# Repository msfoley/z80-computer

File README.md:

# z80-computer
Single board computer based on the Zilog Z80 processor

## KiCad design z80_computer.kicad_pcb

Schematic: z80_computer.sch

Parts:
C1, C3: 22p; CP_Radial_D5.0mm_P2.50mm; Part Number K220J15C0GF5TL2
C2: 100n; CP_Radial_D8.0mm_P5.00mm
C4: 10u; CP_Radial_D8.0mm_P5.00mm
C5: 10u; CP_Radial_D8.0mm_P5.00mm; Part Numer C322C106K3R5TA
J1: Screw_Terminal_01x02; TerminalBlock_RND_205-00001_1x02_P5.00mm_Horizontal
J2: Bus_ISA_8bit; PinHeader_2x31_P2.54mm_Vertical
R1: 1M; R_Axial_DIN0207_L6.3mm_D2.5mm_P5.08mm_Vertical; Part Number CF14JT1M00
R2: 1k; R_Axial_DIN0207_L6.3mm_D2.5mm_P5.08mm_Vertical; Part Number CF14JT1K00
R3: 720; R_Axial_DIN0207_L6.3mm_D2.5mm_P5.08mm_Vertical
R4: 240; R_Axial_DIN0207_L6.3mm_D2.5mm_P5.08mm_Vertical
R5, R6, R7, R8: 10k; R_Axial_DIN0207_L6.3mm_D2.5mm_P5.08mm_Vertical; Part Number CF14JT10K0
R9: 10K; R_Axial_DIN0207_L6.3mm_D2.5mm_P5.08mm_Vertical
U1: 74LS14; DIP-14_W7.62mm
U2: MCP130; TO-92
U3: LM117_TO3; TO-3
U5: Z80CPU; DIP-40_W15.24mm
U8: 74138; DIP-16_W7.62mm
Y1: Crystal; Crystal_HC49-U_Vertical; Part Number GB1000015

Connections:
+5V: C4.1, C5.2, J2.3, J2.29, R4.1, R5.1, R6.1, R7.1, R8.1, U1.14 (VCC), U2.2, U3.3 (VO), U5.11, U8.16; also elsewhere on the board
/A0: J2.62, U5.30
/A1: J2.61, U5.31
/A2: J2.60, U5.32
/A3: J2.59, U5.33
/A4: J2.58, U5.34
/A5: J2.57, U5.35, U8.1
/A6: J2.56, U5.36, U8.2
/A7: J2.55, U5.37, U8.3
/A8: J2.54, U5.38
/A9: J2.53, U5.39
/A10: J2.52, U5.40
/A11: J2.51, U5.1
/A12: J2.50, U5.2
/A13: J2.49, U5.3
/A14: J2.48, U5.4
/A15: J2.47, U5.5
/D0: J2.40, U5.14
/D1: J2.39, U5.15
/D2: J2.38, U5.12
/D3: J2.37, U5.8
/D4: J2.36, U5.7
/D5: J2.35, U5.9
/D6: J2.34, U5.10
/D7: J2.33, U5.13
/DS0: U8.15
/DS1: U8.14
/DS2: U8.13
/DS3: U8.12
/DS4: U8.11
/DS5: U8.10
/DS6: U8.9
/DS7: U8.7
/~BUSACK: U5.23
/~BUSRQ: R8.2, U5.25
/~CLK: J2.20, U1.4, U5.6
/~HALT: U5.18
/~INT: R7.2, U5.16
/~IORD: J2.14; also elsewhere on the board
/~IORQ: U5.20, U8.4, U8.5; also elsewhere on the board
/~IOWR: J2.13; also elsewhere on the board
/~M1: U5.27; also elsewhere on the board
/~MEMRD: J2.12; also elsewhere on the board
/~MEMWR: J2.11; also elsewhere on the board
/~MREQ: U5.19; also elsewhere on the board
/~NMI: R6.2, U5.17
/~RD: U5.21; also elsewhere on the board
/~RFSH: U5.28
/~RST: J2.2, U2.1, U5.26; also elsewhere on the board
/~WAIT: R5.2, U5.24
/~WR: U5.22; also elsewhere on the board
GND: C1.2, C2.2, C3.2, C4.2, C5.1, J1.1, J2.1, J2.10, J2.31, J2.43, J2.44, J2.45, J2.46, R3.2, R9.2, U1.7 (GND), U2.3, U5.29, U8.8; also elsewhere on the board
unnamed: C1.1, R1.1, U1.1, Y1.1
unnamed: C2.1, J1.2, U3.2 (VI)
unnamed: C3.1, R2.2, Y1.2
unnamed: R1.2, R2.1, U1.2, U1.3
unnamed: R3.1, R4.2, U3.1 (ADJ)
unnamed: R9.1, U8.6

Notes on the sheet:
Use a flip flop as the boot ROM/RAM bank switcher, disable input to the bank switcher when the flip flop is asserted.

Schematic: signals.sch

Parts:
U4, U6: 74LS32; DIP-14_W7.62mm

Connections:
+5V: U4.14, U6.9, U6.14; also elsewhere on the board
/~BOOT: U6.13; also elsewhere on the board
/~INTACK: U6.6
/~IORD: U4.6; also elsewhere on the board
/~IORQ: U4.1, U4.4, U6.5; also elsewhere on the board
/~IOWR: U4.3, U6.12; also elsewhere on the board
/~M1: U6.1, U6.4; also elsewhere on the board
/~MEMRD: U4.11; also elsewhere on the board
/~MEMWR: U4.8; also elsewhere on the board
/~MREQ: U4.9, U4.12, U6.2; also elsewhere on the board
/~OPFETCH: U6.3
/~RD: U4.5, U4.13; also elsewhere on the board
/~WR: U4.2, U4.10; also elsewhere on the board
GND: U4.7, U6.7; also elsewhere on the board
unnamed 84: U6.8; also elsewhere on the board
unnamed: U6.10, U6.11

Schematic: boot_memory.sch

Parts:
U6: 74LS32; DIP-14_W7.62mm
U7: 74LS73; DIP-14_W7.62mm

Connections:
+5V: U6.9, U6.14, U7.4, U7.7; also elsewhere on the board
/~BOOT: U6.13, U7.9
/~INTACK: U6.6
/~IORQ: U6.5; also elsewhere on the board
/~IOWR: U6.12; also elsewhere on the board
/~M1: U6.1, U6.4; also elsewhere on the board
/~MREQ: U6.2; also elsewhere on the board
/~OPFETCH: U6.3
/~RST: U7.6; also elsewhere on the board
GND: U6.7, U7.10, U7.11; also elsewhere on the board
unnamed: U6.8, U7.5
unnamed: U6.10, U6.11

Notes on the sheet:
Address select for the boot latch
Boot RAM/ROM go here

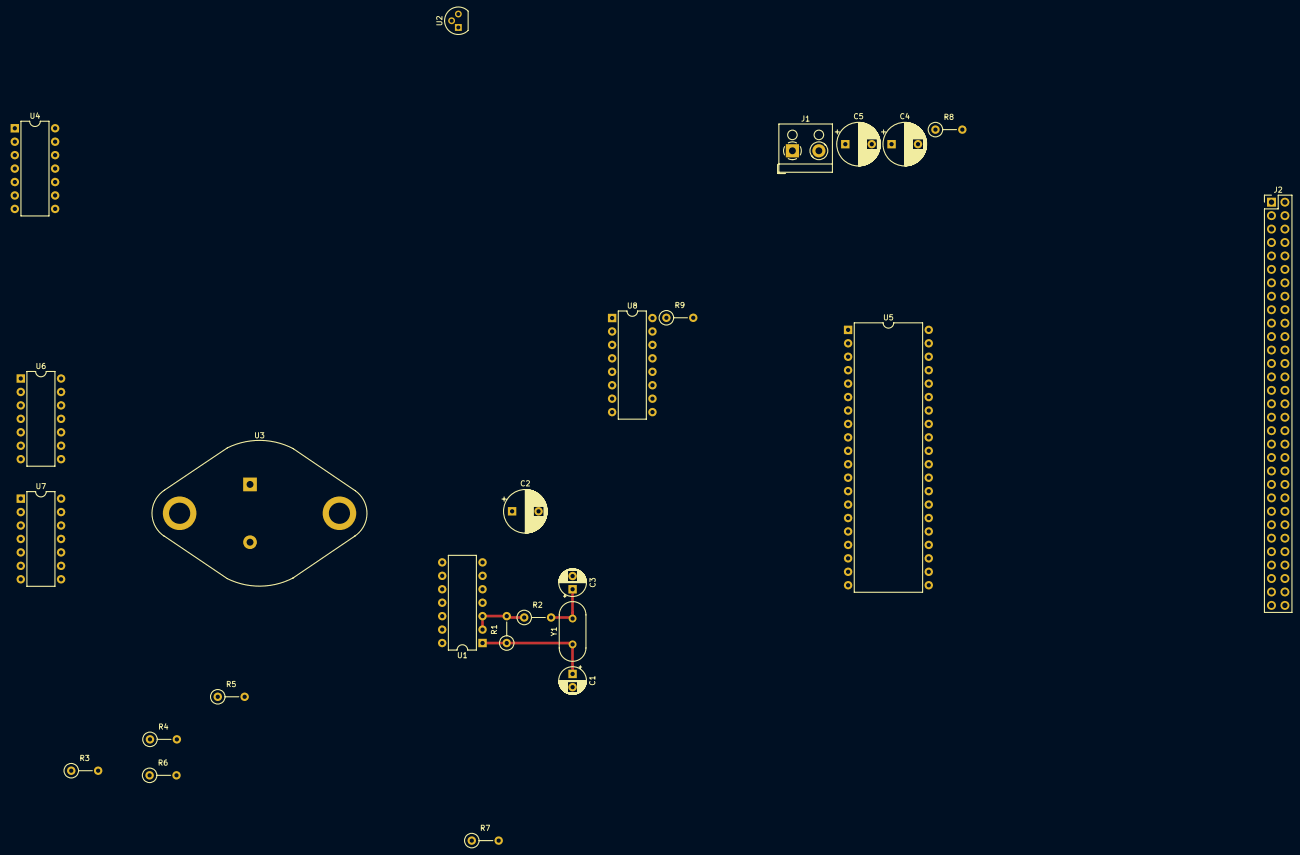
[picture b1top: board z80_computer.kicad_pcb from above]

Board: 4 copper layers, 25 parts (0 on the bottom side), 50 nets.

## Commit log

2018-10-08 Create LICENSE
2018-10-09 Added ISA bus, broke some circuits into sub schematics.
2018-10-09 Added demux for IO select
2018-10-10 Added some temporary footprints and messed with the oscillator layout
